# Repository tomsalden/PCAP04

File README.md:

# ESP32 firmware for the PCAP04

This project has been written as part of a Master's Thesis at the [University of Technology in Delft](https://www.tudelft.nl/). The thesis is based around a Silicon Carbide MEMS pressure sensor. This sensor is a capacitor-based sensor and to read it out, a Capacitor-to-digital converter is necessary. The PCAP04 should work really well due to its high accuracy and resolution. In addition, because it can measure up to 6 capacitances and compare it to one reference capacitance, it is ideal for multiple sensors in the same envionment.
A PlatformIO project has been added to this repository for easy deployment of the code. This contains the latest code written.

# Connecting to the PCAP04

This firmware is written for the ESP32 DevKit-WROOM (available in the Makerspace from the Electrical Engineering Study Association: [Klushok](https://klushok.etv.tudelft.nl/)).

The heart of the firmware uses a library written by Törehan. It has been rewritten to let it make use of I2C in stead of SPI. The reason is that SPI would not work consistenly for my set-up.
The original library can be found on his [GitHub page](https://github.com/torehan/pcap04-arduino).

An example of his integration of the library is visible on his [Metsensor page](https://github.com/torehan/metsensor-pio)

The firmware was first developed for the [PCAP04-EVA-Kit](https://nl.mouser.com/ProductDetail/ScioSense/PCAP04-EVA-KIT?qs=YCa%2FAAYMW01pCMwt%2Fq6O1Q%3D%3D). Later on, the firmware is updated for usage of a custom PCB. In theory, the EVA-Kit should still work with some small modifications. The pinout and further instructions can be found from the section [PCAP04-EVA-board instructions](OldReadme.md). The next sections describe the project using the custom PCB.

# Custom measurement PCB

The PCB has space for three PCAP04 CDC's. Each CDC can read 4 to 5 capacitances and has 1 reference capacitor to make sure the base value is correct.
1 Li-Ion battery will be attached at the back to power the board. Afterwards, the battery is protected and the voltage is boosted to 5V with a HW-775.
As an alternative, one PCAP04 EVA Board can be used instead of one PCAP04 bare chip.

The frontside of the PCB:

The backside of the PCB:

The PCB design includes the following features:

- 3 PCAP04 (or older) measurement chips.
- 1 PCAP04 chip can be replaced with a PCAP04-EVA-BOARD (for testing purposes)
- 3 on-PCB reference capacitors
- 15 (grounded) capacitor measurement possibilities
- Optional offset capacitors can be placed

<!-- -->

- 2 lines for piezoresistive readout are added using voltage dividers
- External resistors can be placed for the voltage division

<!-- -->

- ESP32-Wroom to connect to the PCAP04 chips and process the data
- Micro-SD card holder to save the data
- Power LED directly connected to power line
- RGB Led that is controlled by the ESP32
- 2 multipurpose buttons (start/stop measurements etc.)
- Temperature sensor to keep track of ambient temperature

<!-- -->

- On-off switch breaking the power line
- Can be powered by 2x Li-Ion 18650 batteries (No protection circuitry, use at own risk! Reverse polarity protection is included)
- Cam also be powered by 5V USB line in ESP32-wroom

The Bill of Materials can be found [here]([PCB/PCAP04_Interface/bom/ibom.html](https://tomsalden.github.io/PCAP04/PCB/PCAP04_Interface/bom/ibom.html)) and the order list is placed [here](PCB/PCAP04_Interface/bom/Farnell_Order_List.xlsx).

# Programming instructions
The project has been included in a PlatformIO folder. To setup the workspace, PlatformIO has to be downloaded and this folder has to be imported as a project. This should automatically set the correct libraries and settings. The firmware can be uploaded to an ESP-32 once the project has been imported.

# Program Instructions
Once the firmware has been compiled and uploaded and the PCB has been manufactured, the measurement PCB is ready to start measuring. Place an empty SD card in the SD card slot. Put in a battery in the holder and turn on the switch. The PCB will start its measurements.

## First run
 When the system is turned on, first the program will generate configuration files. Four configuration files in total, one for each PCAP04 chip and one general configuration file.
 
 The general configuration file will define the wifi network the system will try to connect to. The PCAP configuration files define the configuration that can be changed in the webserver.
 
 After this, the system will start with the default settings. It will search for a Wifi Network called "GenericWifi-SSID" with the password "GenericWifi-PWD". If this is not found, then it will create a hotspot.
 Afterwards, the system will apply the default configuration for the PCAP chips and startup a webserver. This can be accessed at the address "192.168.4.1".

 ## Further operation
 Once the system has been stared once, the general configurations file can be edited to let the ESP32 connect to a specified wifi network at startup. If this is not found, the system will create a hotspot.

 Any changes in the webserver settings will immediately be written to the SD card in the corresponding configuration file. This means that at startup, the chips will be loaded with the newest configuration.

 ## Data
 The ESP32 collects the data from all chips. In addition, the system will print a time and a temperature at the time of the measurement. The data file that is generated is a text-based file that can be interpreted as a csv file.

 ### Time
 The measurement of the chips are timed, and the output that will be written will correspond to the time they are taken.
 Because the system does not have a Real Time Clock (RTC), the ESP32 does not know the time at startup. Therefore, the default time is set at October 18 2022 at 0:00. To set the time and date to the correct moment, connect to the webserver and press the "Set Current Time" button. From that moment on, the time will be synchronised with the device that pressed on that button until the ESP32 is restarted.

 ### Temperature
 The temperature on the PCB is measured using a MCP-9701. The voltage reading is converted to a temperature and saved in the data files.

 ### Capacitance data
 The capacitance of each pin of every PCAP chip is read out as fast as possible. When this is done, the data is collected and written to the data file.

## Indication LED
The PCB features an indication LED. This LED shows the status of the program.
After startup and configuration, the measurement starts and the LED will blink blue-green.

# Features and Future improvements

✅Ability to connect to and read data from PCAP04

✅Ability to change I2C address on demand

✅Read data synchronously with PCAP04, as recommended in the datasheet

✅Add SD-card to the system to log data

✅Place PCAP04 settings file on SD card

✅Create a PCB for this system

✅Edit PCAP04 settings without reflashing ESP32

✅Create webserver-based interface for ESP32 (for config changes)

✅Allow for three PCAP04 devices at the same time

✅Clean up code for deployment

⬜️~~Automatically change output format depending on mode selection~~

⬜️~~Make a csv file automatically from the output~~

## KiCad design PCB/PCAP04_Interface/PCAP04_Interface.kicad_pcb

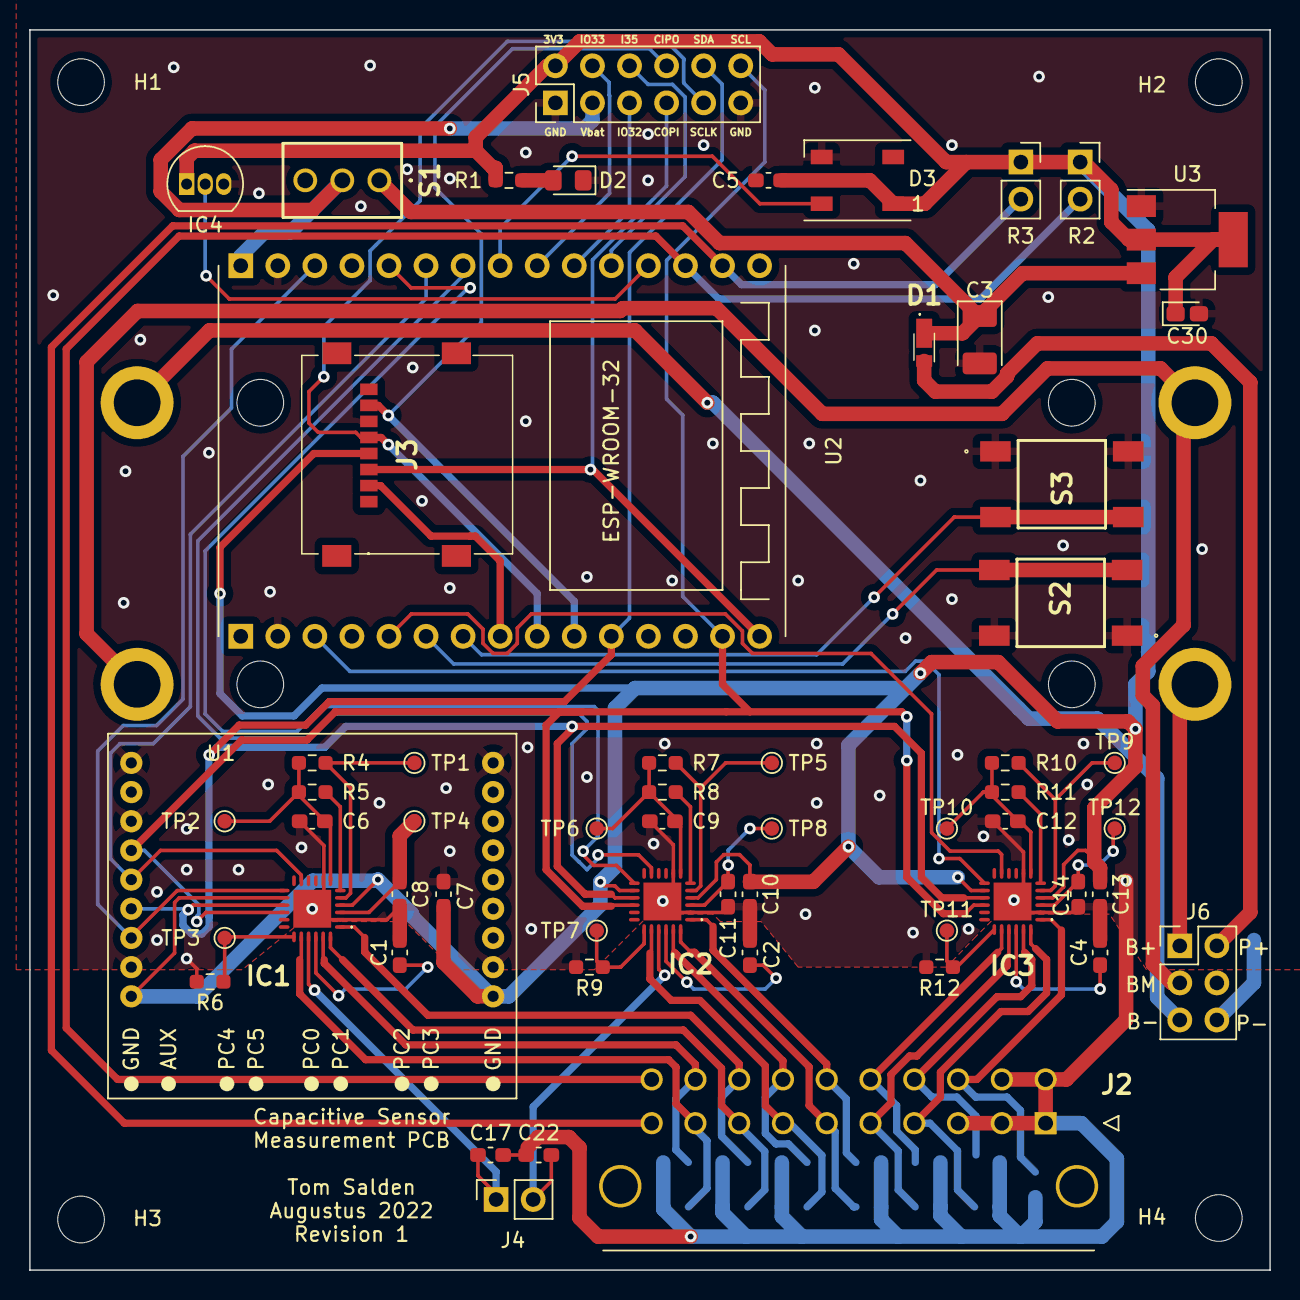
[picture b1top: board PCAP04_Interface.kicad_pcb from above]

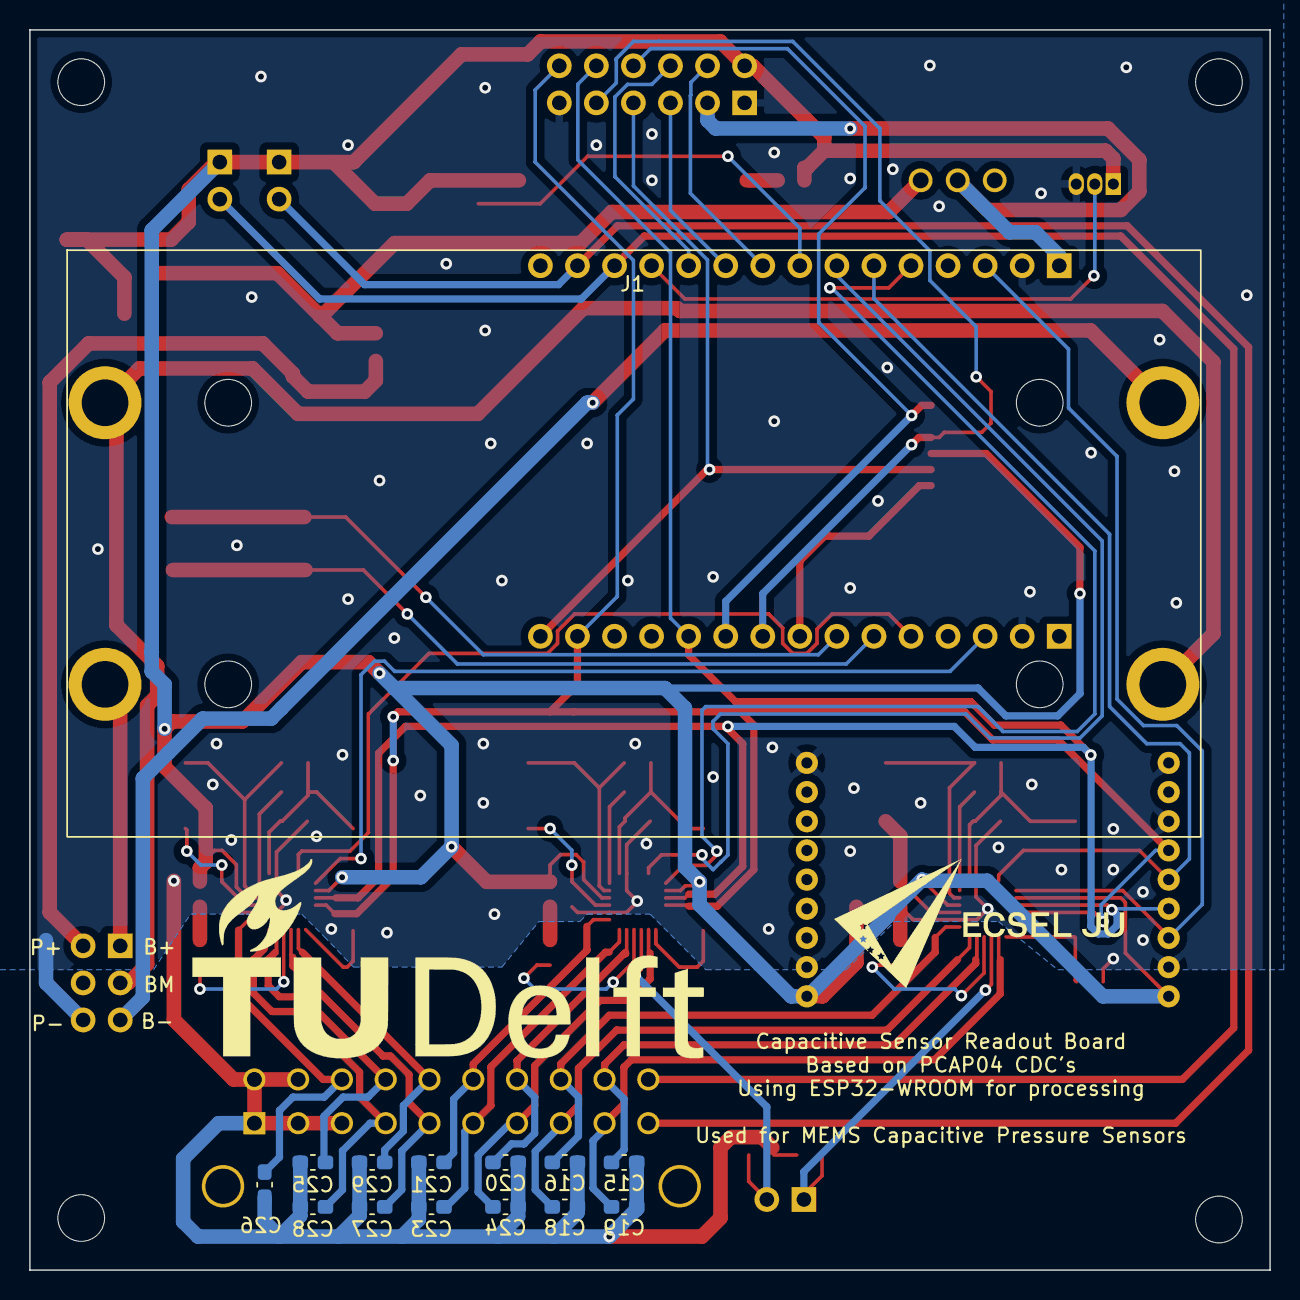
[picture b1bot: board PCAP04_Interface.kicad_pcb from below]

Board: 2 copper layers, 85.0 x 85.0 mm, 77 parts (14 on the bottom side), 63 nets.

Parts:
C1, C2, C4: 2p; C_0603_1608Metric_Pad1.08x0.95mm_HandSolder
C3: 10u; CP_EIA-3528-15_AVX-H_Pad1.50x2.35mm_HandSolder
C5: 100nF; C_0603_1608Metric_Pad1.08x0.95mm_HandSolder
C6, C9, C12: 10n; C_0603_1608Metric_Pad1.08x0.95mm_HandSolder
C7, C10, C13: 10u; C_0603_1608Metric_Pad1.08x0.95mm_HandSolder
C8, C11, C14: 4.7u; C_0603_1608Metric_Pad1.08x0.95mm_HandSolder
C15, C16, C17, C18, C19, C20, C21, C22, C23, C24, C25, C26, C27, C28, C29: C; C_0603_1608Metric_Pad1.08x0.95mm_HandSolder
C30: 22u; CP_EIA-1608-10_AVX-L_Pad1.25x1.05mm_HandSolder
D1: CUHS20S30,H3F; CUHS20S40H3F
D2: LED; LED_0805_2012Metric_Pad1.15x1.40mm_HandSolder
D3: WS2812B; LED_WS2812B_PLCC4_5.0x5.0mm_P3.2mm
H1, H2, H3, H4: MountingHole; MountingHole_3.2mm_M3
IC1, IC2, IC3: PCAP04-AQFM-24; PCAP04AQFM24
IC4: MCP9701-E_TO; TO-92_Inline
J1: Conn_01x04; BK-18650-PC4
J2: 43045-2022; 43045-20_21,22,23_
J3: MEM2067-02-180-00-A; MEM20670218000A
J4: Conn_01x02; PinSocket_1x02_P2.54mm_Vertical
J5: Conn_02x06_Odd_Even; PinHeader_2x06_P2.54mm_Vertical
J6: Conn_02x03_Odd_Even; PinHeader_2x03_P2.54mm_Vertical
R1: 100; R_0603_1608Metric_Pad0.98x0.95mm_HandSolder
R2, R3: R; PinSocket_1x02_P2.54mm_Vertical
R4, R5, R6, R7, R8, R9, R10, R11, R12: nc; R_0603_1608Metric_Pad0.98x0.95mm_HandSolder
S1: 2MS1T2B3M2QES
S2, S3: FSM2JSMAATR; FSM2J_1
TP1, TP2, TP3, TP4, TP5, TP6, TP7, TP8, TP9, TP10, TP11, TP12: TestPoint; TestPoint_Pad_D1.0mm
U1: PCAP_04-eva-board
U2: ESP-WROOM-32-DEVBOARD
U3: AMS1117-3.3; SOT-223-3_TabPin2

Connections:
+3V3: C5.1, C7.1, C10.1, C13.1, C30.1, D3.1 (VDD), IC1.4 (VDD33_1), IC1.14 (VDD33_2), IC2.4 (VDD33_1), IC2.14 (VDD33_2), IC3.4 (VDD33_1), IC3.14 (VDD33_2), IC4.1 (VDD), J3.P4 (VDD), J5.2, R1.1, R2.1, R3.1, U1.J1-1 (VDD), U1.J2-1 (VDD), U3.2 (VO)
+6V: J5.3, S1.2 (COM), U2.1 (VIN)
+BATT: C3.1, D1.1, S1.1 (NO), U3.3 (VI)
/PCAP-IC_1/1V8: C8.1, IC1.3 (VDD18), TP4.1
/PCAP-IC_2/1V8: C11.1, IC2.3 (VDD18), TP8.1
/PCAP-IC_3/1V8: C14.1, IC3.3 (VDD18), TP12.1
B+: J1.4, J6.1
B-: J1.1, J6.5
BM: J1.2, J1.3, J6.3
BUTTON1: S2.3, S2.4, U2.21 (IO16/RX2)
BUTTON2: S3.3, S3.4, U2.22 (IO17/TX2)
C1.1: C15.2, IC1.23 (PC1), J2.19
C1.2: C18.2, IC1.24 (PC2), J2.8
C1.3: C16.2, IC1.1 (PC3), J2.18
C1.4: C19.2, IC1.20 (PC4), J2.9
C1.5: C17.2, IC1.21 (PC5), J4.1
C2.1: C20.2, IC2.23 (PC1), J2.17
C2.2: C23.2, IC2.24 (PC2), J2.6
C2.3: C21.2, IC2.1 (PC3), J2.16
C2.4: C24.2, IC2.20 (PC4), J2.7
C2.5: C22.2, IC2.21 (PC5), J4.2
C3.1: C25.2, IC3.23 (PC1), J2.14
C3.2: C28.2, IC3.24 (PC2), J2.4
C3.3: C26.2, IC3.1 (PC3), J2.13
C3.4: C29.2, IC3.20 (PC4), J2.15
C3.5: C27.2, IC3.21 (PC5), J2.5
CREF_1: C1.1, IC1.22 (PC0)
CREF_2: C2.1, IC2.22 (PC0)
CREF_3: C4.1, IC3.22 (PC0)
GND: C1.2, C2.2, C3.2, C4.2, C5.2, C6.2, C7.2, C8.2, C9.2, C10.2, C11.2, C12.2, C13.2, C14.2, C15.1, C16.1, C17.1, C18.1, C19.1, C20.1, C21.1, C22.1, C23.1, C24.1, C25.1, C26.1, C27.1, C28.1, C29.1, C30.2, D2.1 (K), D3.3 (VSS), IC1.2 (GND_1), IC1.8 (GND_2), IC1.25 (EP), IC2.2 (GND_1), IC2.8 (GND_2), IC2.25 (EP), IC3.2 (GND_1), IC3.8 (GND_2), IC3.25 (EP), IC4.3 (GND), J2.1, J2.2, J2.3, J2.11, J2.12, J3.P6 (VSS), J5.1, J5.11, J6.6, R6.2, R9.2, R12.2, S2.1, S2.2, S3.1, S3.2, U1.J1-2 (GND), U1.J1-9 (GND), U1.J2-2 (GND), U1.J2-7 (GND), U1.J2-9 (GND), U2.2 (GND), U2.17 (GND), U3.1 (GND)
I35: J5.6, U2.11 (I35)
IO32: J5.5, U2.10 (IO32)
IO33: J5.4, U2.9 (IO33)
LED_DATA: D3.4 (DIN), U2.8 (IO25)
unnamed: C6.1, IC1.7 (PTOUT), R4.2, R5.2, TP2.1
unnamed: C9.1, IC2.7 (PTOUT), R7.2, R8.2, TP6.1
unnamed: C12.1, IC3.7 (PTOUT), R10.2, R11.2, TP10.1
unnamed: D2.2 (A), R1.2
unnamed: IC1.5 (PT1), R4.1, TP1.1
unnamed: IC1.6 (PT0REF), R5.1
unnamed: IC1.19 (PCAUX), R6.1, TP3.1
unnamed: IC2.5 (PT1), R7.1, TP5.1
unnamed: IC2.6 (PT0REF), R8.1
unnamed: IC2.19 (PCAUX), R9.1, TP7.1
unnamed: IC3.5 (PT1), R10.1, TP9.1
unnamed: IC3.6 (PT0REF), R11.1
unnamed: IC3.19 (PCAUX), R12.1, TP11.1
P+: D1.2, J6.2
PCAP1_EN: IC1.13 (IIC_EN), U1.J2-3 (IIC_EN), U2.3 (IO13/HSPI_MOSI)
PCAP1_INT: IC1.11 (PG5), U1.J2-5 (PG5), U2.6 (IO27)
PCAP2_EN: IC2.13 (IIC_EN), U2.5 (IO14/HSPI_CLK)
PCAP2_INT: IC2.11 (PG5), U2.7 (IO26)
PCAP3_EN: IC3.13 (IIC_EN), U2.18 (IO15/HSPI_CS0)
PCAP3_INT: IC3.11 (PG5), U2.20 (IO04)
PR1-SENSE: J2.20, R2.2, U2.13 (I39/SENSOR_VN)
PR2-SENSE: J2.10, R3.2, U2.14 (I36/SENSOR_VP)
SCL: IC1.16 (SCK_SCL), IC2.16 (SCK_SCL), IC3.16 (SCK_SCL), J5.12, U1.J2-6 (SCL), U2.29 (IO22/SCL)
SDA: IC1.15 (MOSI_SDA), IC2.15 (MOSI_SDA), IC3.15 (MOSI_SDA), J5.10, U1.J2-4 (SDA), U2.26 (IO21/SDA)
SD_CS: J3.P2 (CD/DAT3), U2.23 (IO05/VSPI_CS0)
SD_MISO: J3.P7 (DAT0), J5.8, U2.25 (IO19/VSPI_MISO)
SD_MOSI: J3.P3 (CMD), J5.7, U2.30 (IO23/VSPI_MOSI)
SD_SCLK: J3.P5 (CLK), J5.9, U2.24 (IO18/VSPI_CLK)
V_TEMP: IC4.2 (VOUT), U2.12 (I34)

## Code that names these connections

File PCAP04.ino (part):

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#define ledB 32

//Definitions for SD-Card
#define SD_CS 5

unsigned long current_micros = 0;

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  pcap_config->OLF_FTUNE = 0x07;            //Finetune low frequency clock
  //Reg1 settings
  //Reg2 settings
  pcap_config->RDCHG_INT_SEL1 = 0x00;       //Discharge resistors PC4-PC5
  pcap_config->RDCHG_INT_SEL0 = 0x00;       //Discharge resistors PC0-3 plus PC6
  pcap_config->RDCHG_INT_EN = 0x01;         //Enable internal discharge resistors
  //Reg3 settings
  pcap_config->RCHG_SEL = 0x00;             //Charging resistors to limit charging
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  //Reg24, 25, 26 settings (Mandatory bits)
  //Reg27-29 settings
  //Reg30 settings
  pcap_config->PG5_INTN_EN = true;          //Route INTN signal to PG5
  //Reg35 settings
  pcap_config->CDC_GAIN_CORR = 0x40;        //Firmware defined gain correlation factor
  //Reg29 settings
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
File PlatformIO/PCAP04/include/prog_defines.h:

#ifndef prog_defines_h
#define prog_defines_h

//Definitions for PCAP pins and addresses
#define pcap1_i2c 13        //I2C enable pin for 1st PCAP
#define pcap2_i2c 14        //I2C enable pin for 2nd PCAP
#define pcap3_i2c 15        //I2C enable pin for 3rd PCAP

#define pcap1_int 27        //DataIsReady from 1st PC
#define pcap2_int 26        //DataIsReady from 2nd PCAP
#define pcap3_int 04        //DataIsReady from 3rd PCAP

#define defaultAddress 0x28  //Default I2C address of PCAP04
#define pcap1_addr 0x29     //I2C address for 1st PCAP
#define pcap2_addr 0x2a     //I2C address for 2nd PCAP
#define pcap3_addr 0x2b     //I2C address for 3rd PCAP

//Definitions for indicator Leds and other interfaces
#define powerLed 27
#define ledR 26
#define ledG 26
#define ledB 26
#define ws2812Led 25
#define tempSensor 34
#define Vpos_C32 35 //commercial absolute pressure sensor
#define Vneg_C32 32 //commerical absolute pressure sensor

#define C32_sensitivity 23  //in mV/bar

//Definitions for SD-Card
#define SD_CS 5


#endif

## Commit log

2022-07-06 Created rudamentary first version
2022-07-06 Added interfacing information to readme
2022-07-06 Removed unnecessary files
2022-07-07 Removed extra line in output, updated readme
2022-07-07 Added asynchronous readout
2022-07-07 Edited readme
2022-07-07 Updated an old comment
2022-07-07 Fixed mistake in readme
2022-07-07 Changed initialisation led color to blue
2022-07-07 Removed personal folder
2022-07-07 Moved datasheet to a proper location
2022-07-07 Added pinout image of ESP32
2022-07-07 Added pinout for PCAP04
2022-07-08 Added pinout for SD card
2022-07-08 Added SD-card support to write data
2022-08-02 Add ability to change I2C Address
2022-08-02 Created Measurement PCB
2022-08-02 Edited PCB so battery is on the back
2022-08-02 Added logos and text on PCB
2022-08-02 Added breakout for C1.5 and C2.5, updated readme
2022-08-02 Added breakout for C1.5 and C2.5
2022-08-02 Testing webserver features
2022-08-03 Created simple webserver, updated PCB
2022-08-04 Created PlatformIO-based project
2022-08-05 Upgraded webserver functionalities
2022-08-16 Poging tot config
2022-08-16 Create working configuration save
2022-08-23 WorkingConfig
2022-09-05 Changed battery circuitry
2022-09-05 Changed Boost circuit
2022-09-05 Extra save
2022-09-05 Add new workspace to the folder
2022-09-05 Added Thesis folder to workspace
2022-09-05 Updated PCB images for readme
2022-09-05 Updated readme to the current state
2022-09-05 The readme is updated to the current state
2022-09-05 Cleaned up old files
2022-09-05 Changed location of included files
2022-09-05 Edited order list for components
2022-09-06 Slightly cleaned up code
2022-09-06 Cleaned up main.cpp
2022-09-06 Started on framework for multiple PCAP04 devices
2022-09-07 Multiple configurations allowed
2022-09-07 Webserver config allows for multiple PCAP devices
2022-09-07 Prepare for specific output
2022-09-07 Format function better
2022-09-07 Start multiple PCAP results
2022-09-07 Improved index looping
2022-09-08 Allows for multiple PCAP in output
2022-09-08 Webserver updates three PCAP values
2022-09-08 Cleaned up main
2022-09-13 Drastically improved header usage and readability
2022-09-14 Added some comments to improve readability
2022-09-15 Adjusted for physcal test
2022-09-15 Extraconfig modified: PlatformIO/PCAP04/include/SDFunctions.h modified: PlatformIO/PCAP04/include/prog_globals.h modified: PlatformIO/PCAP04/src/SDFunctions.cpp modified: PlatformIO/PCAP04/src/main.c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
    ExtraConfig
2022-09-15 Updated PCB slightly
2022-09-16 Updated calibration features
2022-09-16 Finialised zeroing feature
2022-09-16 Improved multiplication Factor
2022-09-20 Improved extra configuration features
2022-09-21 Added temperature readout
2022-09-21 Added guard options to webserver
2022-09-23 Fixed time and write it to SD
2022-09-23 Added WS2812 functionality as indicator led
2022-09-26 Added an index page for github pages
2022-09-26 Edited reame to get bom link working
2022-12-04 Added readout of commercial pressuresensor
